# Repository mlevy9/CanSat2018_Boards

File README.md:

# CanSat2018_Boards
# Designed by Mecah Levy
#   for  the SDSL Cansat 
#   competition teams for 2018

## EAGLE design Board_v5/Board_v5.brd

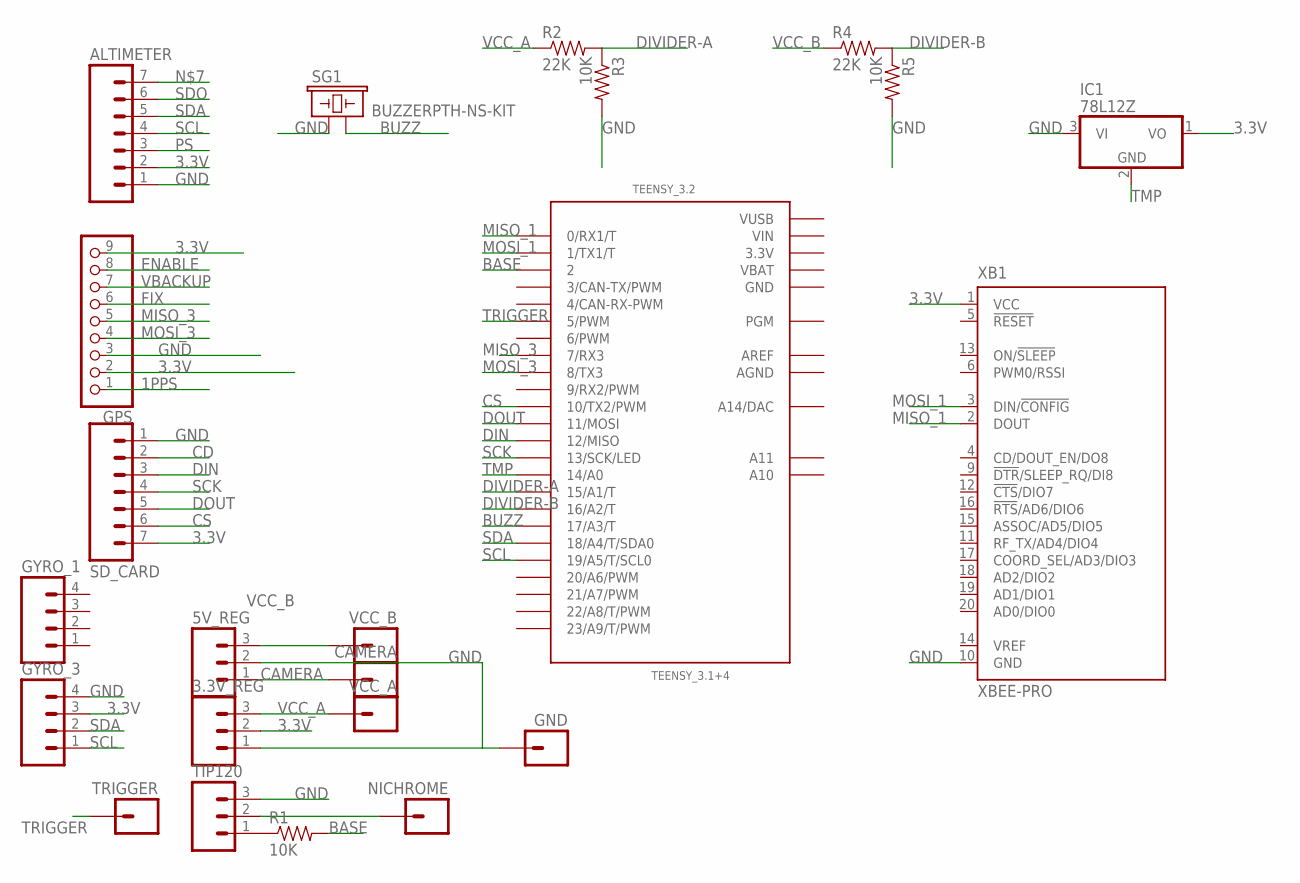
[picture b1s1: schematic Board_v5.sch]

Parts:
3.3V_REG, 5V_REG: M03PTH; 1X03
ALTIMETER: M07; 1X07
CAMERA: M01NOSILK-KIT; 1X01NS-KIT
GND: M01PTH_LONGPAD; 1X01_LONGPAD
GPS: HEADER-1X970MIL; 1X09_ROUND_70
GYRO_1, GYRO_3: M04PTH; 1X04
IC1: 78L12Z; TO92
NICHROME: M01PTH_LONGPAD; 1X01_LONGPAD
R1: 10K; AXIAL-0.3EZ
R2, R4: 22K; AXIAL-0.3
R3, R5: 10K; AXIAL-0.3
SD_CARD: M07; 1X07
SG1: BUZZERPTH-NS-KIT; BUZZER-12MM-NS-KIT
TEENSY_3.2: TEENSY_3.1+4
TIP120: M03PTH; 1X03
TRIGGER: M01NOSILK-KIT; 1X01NS-KIT
VCC_A: M01PTH_LONGPAD; 1X01_LONGPAD
VCC_B: M01OFFSET; 1X01_OFFSET
XB1: XBEE-PRO

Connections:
1PPS: GPS.1
3.3V: 3.3V_REG.2, ALTIMETER.2, GPS.2, GPS.9, GYRO_3.3, IC1.1 (VO), SD_CARD.7, TEENSY_3.2.3.3V, TEENSY_3.2.3.3V1 (3.3V), XB1.1 (VCC)
AGND: TEENSY_3.2.AGND
AREF: TEENSY_3.2.AREF
BASE: R1.P$2 (2), TEENSY_3.2.2
BUZZ: SG1.- (2), TEENSY_3.2.17/A3 (17/A3/T)
CAMERA: 5V_REG.1, CAMERA.1
CD: SD_CARD.2
CS: SD_CARD.6, TEENSY_3.2.10 (10/TX2/PWM)
DIN: SD_CARD.3, TEENSY_3.2.12 (12/MISO)
DIVIDER-A: R2.P$2 (2), R3.P$1 (1), TEENSY_3.2.15/A1 (15/A1/T)
DIVIDER-B: R4.P$2 (2), R5.P$1 (1), TEENSY_3.2.16/A2 (16/A2/T)
DOUT: SD_CARD.5, TEENSY_3.2.11 (11/MOSI)
ENABLE: GPS.8
FIX: GPS.6
GND: 3.3V_REG.1, 5V_REG.2, ALTIMETER.1, GND.1, GPS.3, GYRO_3.4, IC1.3 (VI), R3.P$2 (2), R5.P$2 (2), SD_CARD.1, SG1.+ (1), TEENSY_3.2.GND, TEENSY_3.2.GND1 (GND), TIP120.3, XB1.10 (GND)
MISO_1: TEENSY_3.2.0 (0/RX1/T), XB1.2 (DOUT)
MISO_3: GPS.5, TEENSY_3.2.7 (7/RX3)
MOSI_1: TEENSY_3.2.1 (1/TX1/T), XB1.3 (DIN/!CONFIG)
MOSI_3: GPS.4, TEENSY_3.2.8 (8/TX3)
unnamed: R1.P$1 (1), TIP120.1
NICHROME: NICHROME.1, TIP120.2
PS: ALTIMETER.3
SCK: SD_CARD.4, TEENSY_3.2.13 (13/SCK/LED)
SCL: ALTIMETER.4, GYRO_3.1, TEENSY_3.2.19/A5 (19/A5/T/SCL0)
SDA: ALTIMETER.5, GYRO_3.2, TEENSY_3.2.18/A4 (18/A4/T/SDA0)
SDO: ALTIMETER.6
TMP: IC1.2 (GND), TEENSY_3.2.14/A0
TRIGGER: TEENSY_3.2.5 (5/PWM), TRIGGER.1
VBACKUP: GPS.7
VBAT: TEENSY_3.2.VBAT
VCC_A: 3.3V_REG.3, R2.P$1 (1), VCC_A.1
VCC_B: 5V_REG.3, R4.P$1 (1), VCC_B.1
VIN: TEENSY_3.2.VIN
VUSB: TEENSY_3.2.VUSB

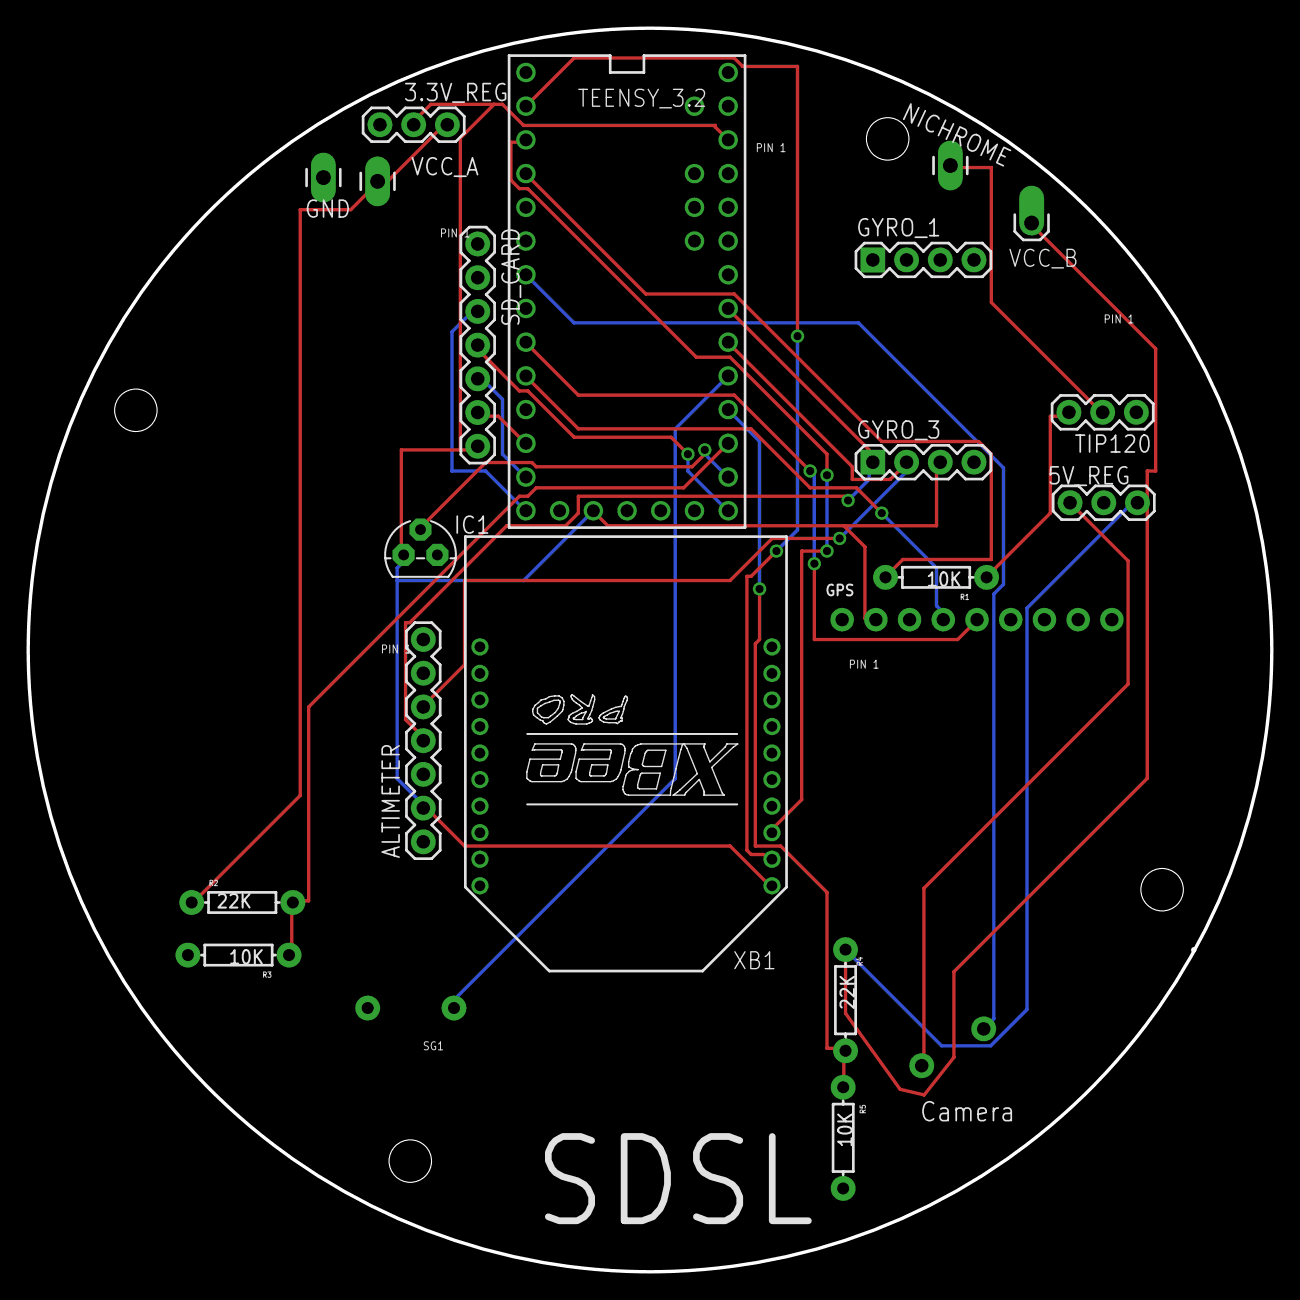
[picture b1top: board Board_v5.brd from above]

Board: 2 copper layers, 93.5 x 93.5 mm, 23 parts (0 on the bottom side), 23 nets.

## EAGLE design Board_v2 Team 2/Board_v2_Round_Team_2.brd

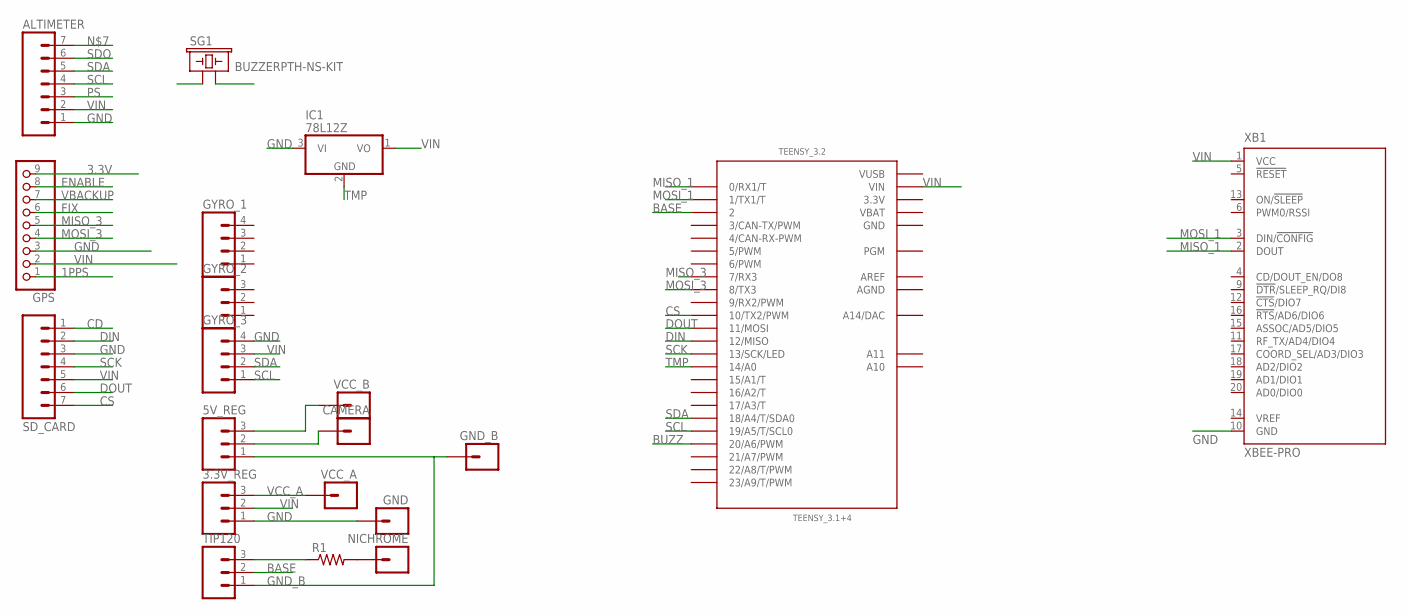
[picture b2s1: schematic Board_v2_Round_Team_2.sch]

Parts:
3.3V_REG, 5V_REG: M03PTH; 1X03
ALTIMETER: M07; 1X07
CAMERA: M01NOSILK-KIT; 1X01NS-KIT
GND: M01PTH_LONGPAD; 1X01_LONGPAD
GND_B: M01OFFSET; 1X01_OFFSET
GPS: HEADER-1X970MIL; 1X09_ROUND_70
GYRO_1, GYRO_3: M04PTH; 1X04
GYRO_2: M03PTH; 1X03
IC1: 78L12Z; TO92
NICHROME: M01OFFSET; 1X01_OFFSET
R1: RESISTOREZ; AXIAL-0.3EZ
SD_CARD: M07; 1X07
SG1: BUZZERPTH-NS-KIT; BUZZER-12MM-NS-KIT
TEENSY_3.2: TEENSY_3.1+4
TIP120: M03PTH; 1X03
VCC_A: M01PTH_LONGPAD; 1X01_LONGPAD
VCC_B: M01OFFSET; 1X01_OFFSET
XB1: XBEE-PRO

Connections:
1PPS: GPS.1
3.3V: GPS.9, TEENSY_3.2.3.3V, TEENSY_3.2.3.3V1 (3.3V)
AGND: TEENSY_3.2.AGND
AREF: TEENSY_3.2.AREF
BASE: TEENSY_3.2.2, TIP120.2
BUZZ: SG1.+ (1), TEENSY_3.2.20/A6 (20/A6/PWM)
CD: SD_CARD.1
CS: SD_CARD.7, TEENSY_3.2.10 (10/TX2/PWM)
DIN: SD_CARD.2, TEENSY_3.2.12 (12/MISO)
DOUT: SD_CARD.6, TEENSY_3.2.11 (11/MOSI)
ENABLE: GPS.8
FIX: GPS.6
GND: 3.3V_REG.1, ALTIMETER.1, GND.1, GPS.3, GYRO_3.4, IC1.3 (VI), SD_CARD.3, SG1.- (2), TEENSY_3.2.GND, TEENSY_3.2.GND1 (GND), XB1.10 (GND)
GND_B: 5V_REG.1, GND_B.1, TIP120.1
MISO_1: TEENSY_3.2.0 (0/RX1/T), XB1.2 (DOUT)
MISO_3: GPS.5, TEENSY_3.2.7 (7/RX3)
MOSI_1: TEENSY_3.2.1 (1/TX1/T), XB1.3 (DIN/!CONFIG)
MOSI_3: GPS.4, TEENSY_3.2.8 (8/TX3)
unnamed: NICHROME.1, R1.P$2 (2)
unnamed: R1.P$1 (1), TIP120.3
unnamed: 5V_REG.2, CAMERA.1
unnamed: 5V_REG.3, VCC_B.1
PS: ALTIMETER.3
SCK: SD_CARD.4, TEENSY_3.2.13 (13/SCK/LED)
SCL: ALTIMETER.4, GYRO_3.1, TEENSY_3.2.19/A5 (19/A5/T/SCL0)
SDA: ALTIMETER.5, GYRO_3.2, TEENSY_3.2.18/A4 (18/A4/T/SDA0)
SDO: ALTIMETER.6
TMP: IC1.2 (GND), TEENSY_3.2.14/A0
VBACKUP: GPS.7
VBAT: TEENSY_3.2.VBAT
VCC_A: 3.3V_REG.3, VCC_A.1
VIN: 3.3V_REG.2, ALTIMETER.2, GPS.2, GYRO_3.3, IC1.1 (VO), SD_CARD.5, TEENSY_3.2.VIN, XB1.1 (VCC)
VUSB: TEENSY_3.2.VUSB

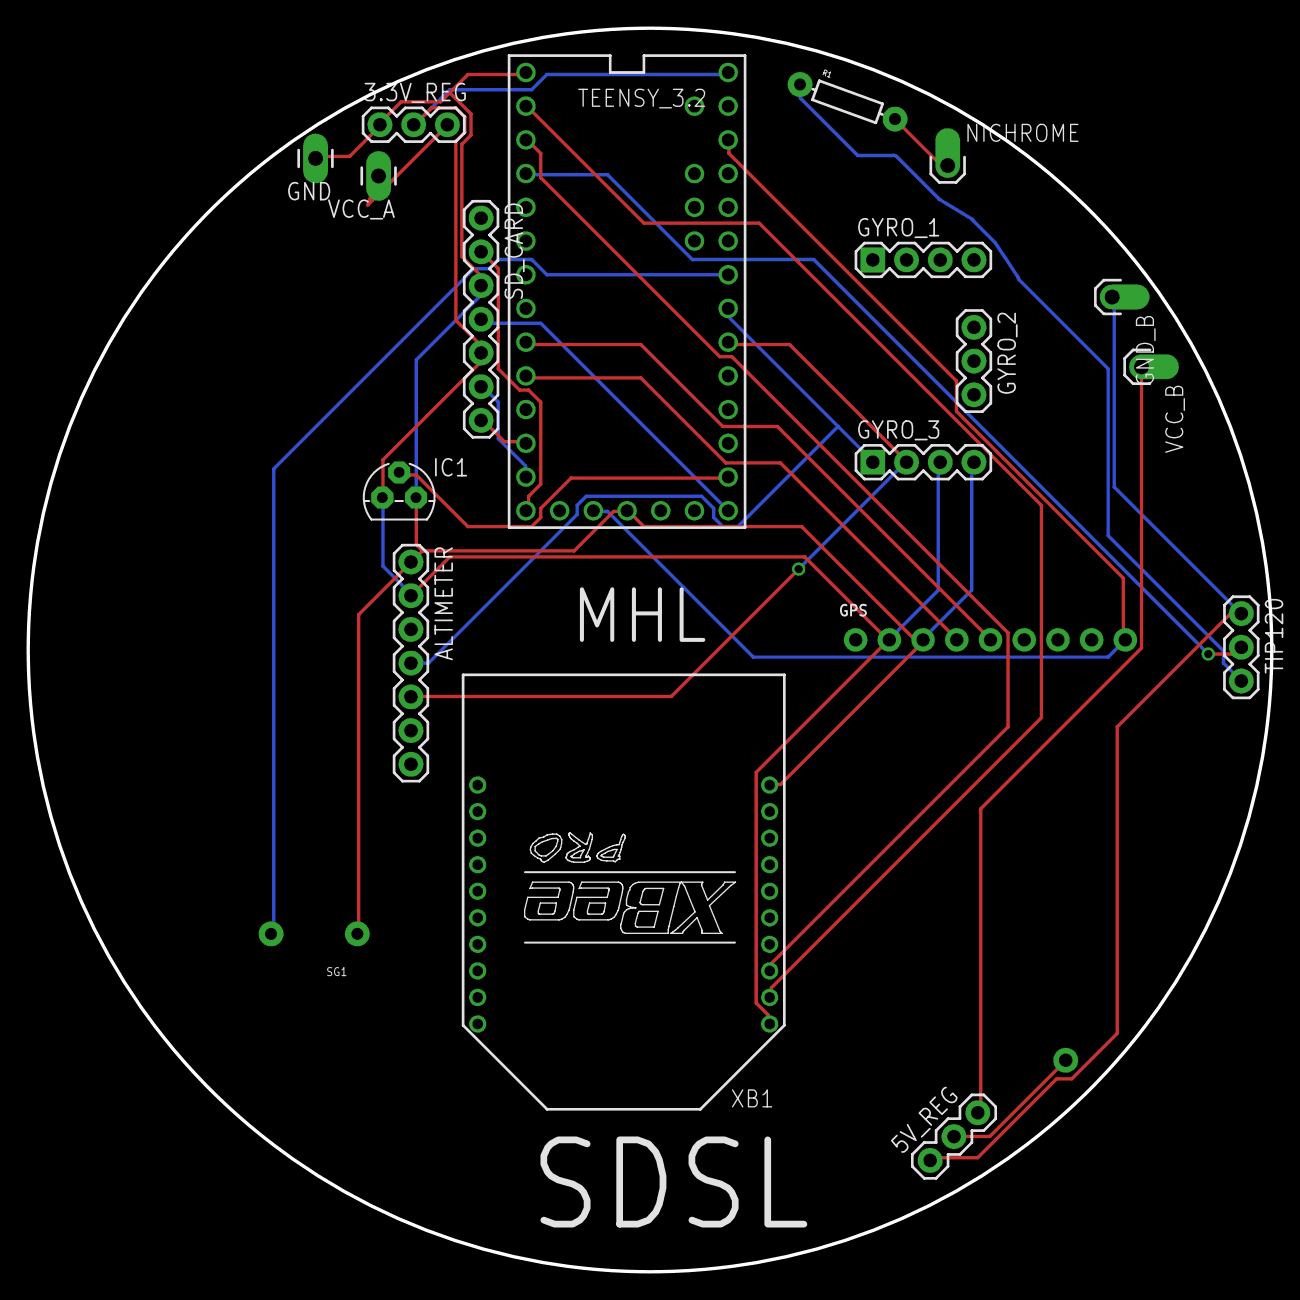
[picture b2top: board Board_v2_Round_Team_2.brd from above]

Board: 2 copper layers, 93.7 x 93.7 mm, 20 parts (0 on the bottom side), 22 nets.

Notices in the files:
parts and their libraries:
SparkFun-Connectors: Licensing: Creative Commons ShareAlike 4.0 International - https://creativecommons.org/licenses/by-sa/4.0
SparkFun: Licensing: CC v3.0 Share-Alike You are welcome to use this library for commercial purposes.
